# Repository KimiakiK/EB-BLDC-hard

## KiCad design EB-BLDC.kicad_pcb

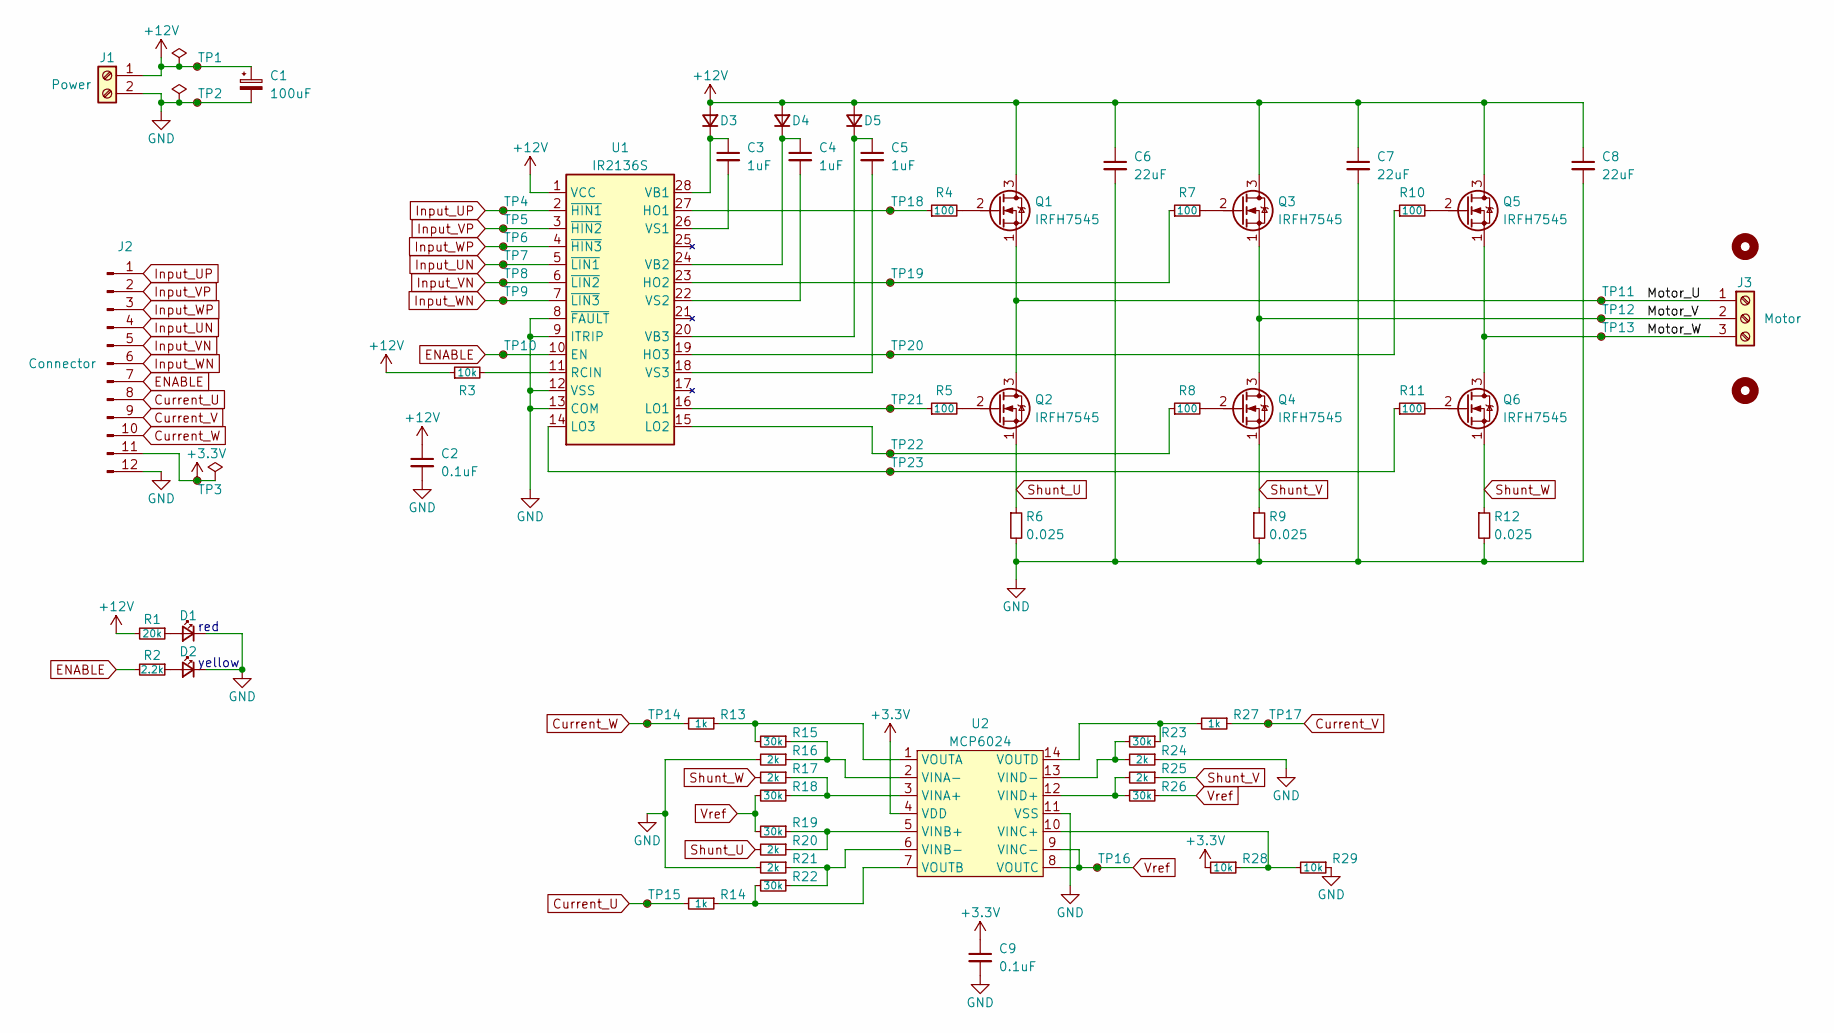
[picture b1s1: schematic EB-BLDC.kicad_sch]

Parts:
C1: 100uF; CP_Elec_6.3x7.7
C2, C9: 0.1uF; 1608Metric
C3, C4, C5: 1uF; 1608Metric
C6, C7, C8: 22uF; 2012Metric
D1, D2: LED; 1608Metric
D3, D4, D5: D; D_SOD-123
H1, H2: MountingHole; MountingHole_3.2mm_M3
J1: Power; TerminalBlock_5.08_1x02_P5.08mm_Horizontal
J2: Connector; PinHeader_2x06_P2.54mm_Horizontal
J3: Motor; TerminalBlock_5.08_1x03_P5.08mm_Horizontal
Q1, Q2, Q3, Q4, Q5, Q6: IRFH7545; VSONP-8-1EP_5x6_P1.27mm
R1: 20k; 1608Metric
R2: 2.2k; 1608Metric
R3, R28, R29: 10k; 1608Metric
R4, R5, R7, R8, R10, R11: 100; 1608Metric
R6, R9, R12: 0.025; R_2512_6332Metric
R13, R14, R27: 1k; 1608Metric
R15, R18, R19, R22, R23, R26: 30k; 1608Metric
R16, R17, R20, R21, R24, R25: 2k; 1608Metric
TP1, TP2, TP3, TP4, TP5, TP6, TP7, TP8, TP9, TP10, TP11, TP12, TP13, TP14, TP15, TP16, TP17, TP18, TP19, TP20, TP21, TP22, TP23: TestPoint; TestPoint_Plated_Hole_D0.8mm
U1: IR2136S; SOIC-28W_7.5x17.9mm_P1.27mm
U2: MCP6024; TSSOP-14_4.4x5mm_P0.65mm

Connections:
+3.3V: C9.1, J2.11, R28.2, TP3.1, U2.4 (VDD)
+12V: C1.1, C2.1, C6.1, C7.1, C8.1, D3.2 (A), D4.2 (A), D5.2 (A), J1.1, Q1.3 (D), Q3.3 (D), Q5.3 (D), R1.2, R3.1, TP1.1, U1.1 (VCC)
/Motor_U: J3.1, Q1.1 (S), Q2.3 (D), TP11.1
/Motor_V: J3.2, Q3.1 (S), Q4.3 (D), TP12.1
/Motor_W: J3.3, Q5.1 (S), Q6.3 (D), TP13.1
Current_U: J2.8, R14.2, TP15.1
Current_V: J2.9, R27.1, TP17.1
Current_W: J2.10, R13.2, TP14.1
ENABLE: J2.7, R2.2, TP10.1, U1.10 (EN)
GND: C1.2, C2.2, C6.2, C7.2, C8.2, C9.2, D1.1 (K), D2.1 (K), J1.2, J2.12, R6.2, R9.2, R12.2, R16.2, R21.2, R24.1, R29.1, TP2.1, U1.8 (~FAULT), U1.9 (ITRIP), U1.12 (VSS), U1.13 (COM), U2.11 (VSS)
Input_UN: J2.4, TP7.1, U1.5 (~LIN1)
Input_UP: J2.1, TP4.1, U1.2 (~HIN1)
Input_VN: J2.5, TP8.1, U1.6 (~LIN2)
Input_VP: J2.2, TP5.1, U1.3 (~HIN2)
Input_WN: J2.6, TP9.1, U1.7 (~LIN3)
Input_WP: J2.3, TP6.1, U1.4 (~HIN3)
unnamed: D1.2 (A), R1.1
unnamed: D2.2 (A), R2.1
unnamed: C3.1, D3.1 (K), U1.28 (VB1)
unnamed: C4.1, D4.1 (K), U1.24 (VB2)
unnamed: C5.1, D5.1 (K), U1.20 (VB3)
unnamed: Q1.2 (G), R4.2
unnamed: Q2.2 (G), R5.2
unnamed: Q3.2 (G), R7.2
unnamed: Q4.2 (G), R8.2
unnamed: Q5.2 (G), R10.2
unnamed: Q6.2 (G), R11.2
unnamed: R4.1, TP18.1, U1.27 (HO1)
unnamed: R7.1, TP19.1, U1.23 (HO2)
unnamed: R10.1, TP20.1, U1.19 (HO3)
unnamed: R5.1, TP21.1, U1.16 (LO1)
unnamed: R8.1, TP22.1, U1.15 (LO2)
unnamed: R11.1, TP23.1, U1.14 (LO3)
unnamed: R3.2, U1.11 (RCIN)
unnamed: C3.2, U1.26 (VS1)
unnamed: C4.2, U1.22 (VS2)
unnamed: C5.2, U1.18 (VS3)
unnamed: R17.1, R18.1, U2.3 (VINA+)
unnamed: R15.1, R16.1, U2.2 (VINA-)
unnamed: R19.1, R20.1, U2.5 (VINB+)
unnamed: R21.1, R22.1, U2.6 (VINB-)
unnamed: R28.1, R29.2, U2.10 (VINC+)
unnamed: R25.2, R26.2, U2.12 (VIND+)
unnamed: R23.2, R24.2, U2.13 (VIND-)
unnamed: R13.1, R15.2, U2.1 (VOUTA)
unnamed: R14.1, R22.2, U2.7 (VOUTB)
unnamed: R23.1, R27.2, U2.14 (VOUTD)
Shunt_U: Q2.1 (S), R6.1, R20.2
Shunt_V: Q4.1 (S), R9.1, R25.1
Shunt_W: Q6.1 (S), R12.1, R17.2
Vref: R18.2, R19.2, R26.1, TP16.1, U2.8 (VOUTC), U2.9 (VINC-)

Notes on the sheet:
yellow
red

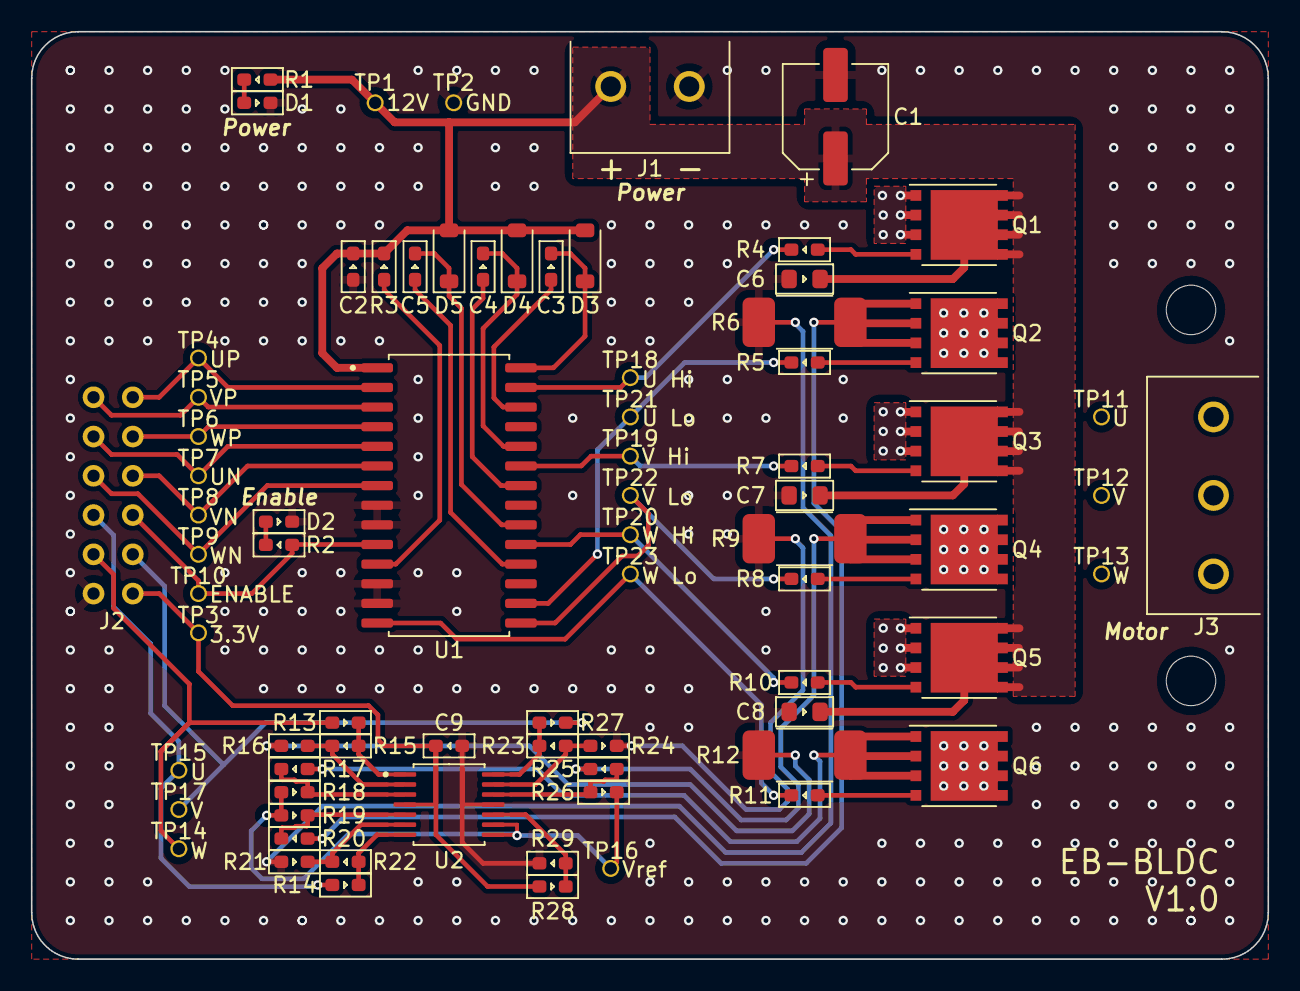
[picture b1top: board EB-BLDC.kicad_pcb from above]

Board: 2 copper layers, 80.0 x 60.0 mm, 79 parts (0 on the bottom side), 51 nets.

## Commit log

2023-12-17 基板 V1.0
2024-01-11 回路図追加
